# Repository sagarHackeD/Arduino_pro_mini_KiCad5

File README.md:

# Arduino_pro_mini_KiCad5
Arduino pro mini project in kicad 5

https://youtu.be/w0Ov9XtYdCo

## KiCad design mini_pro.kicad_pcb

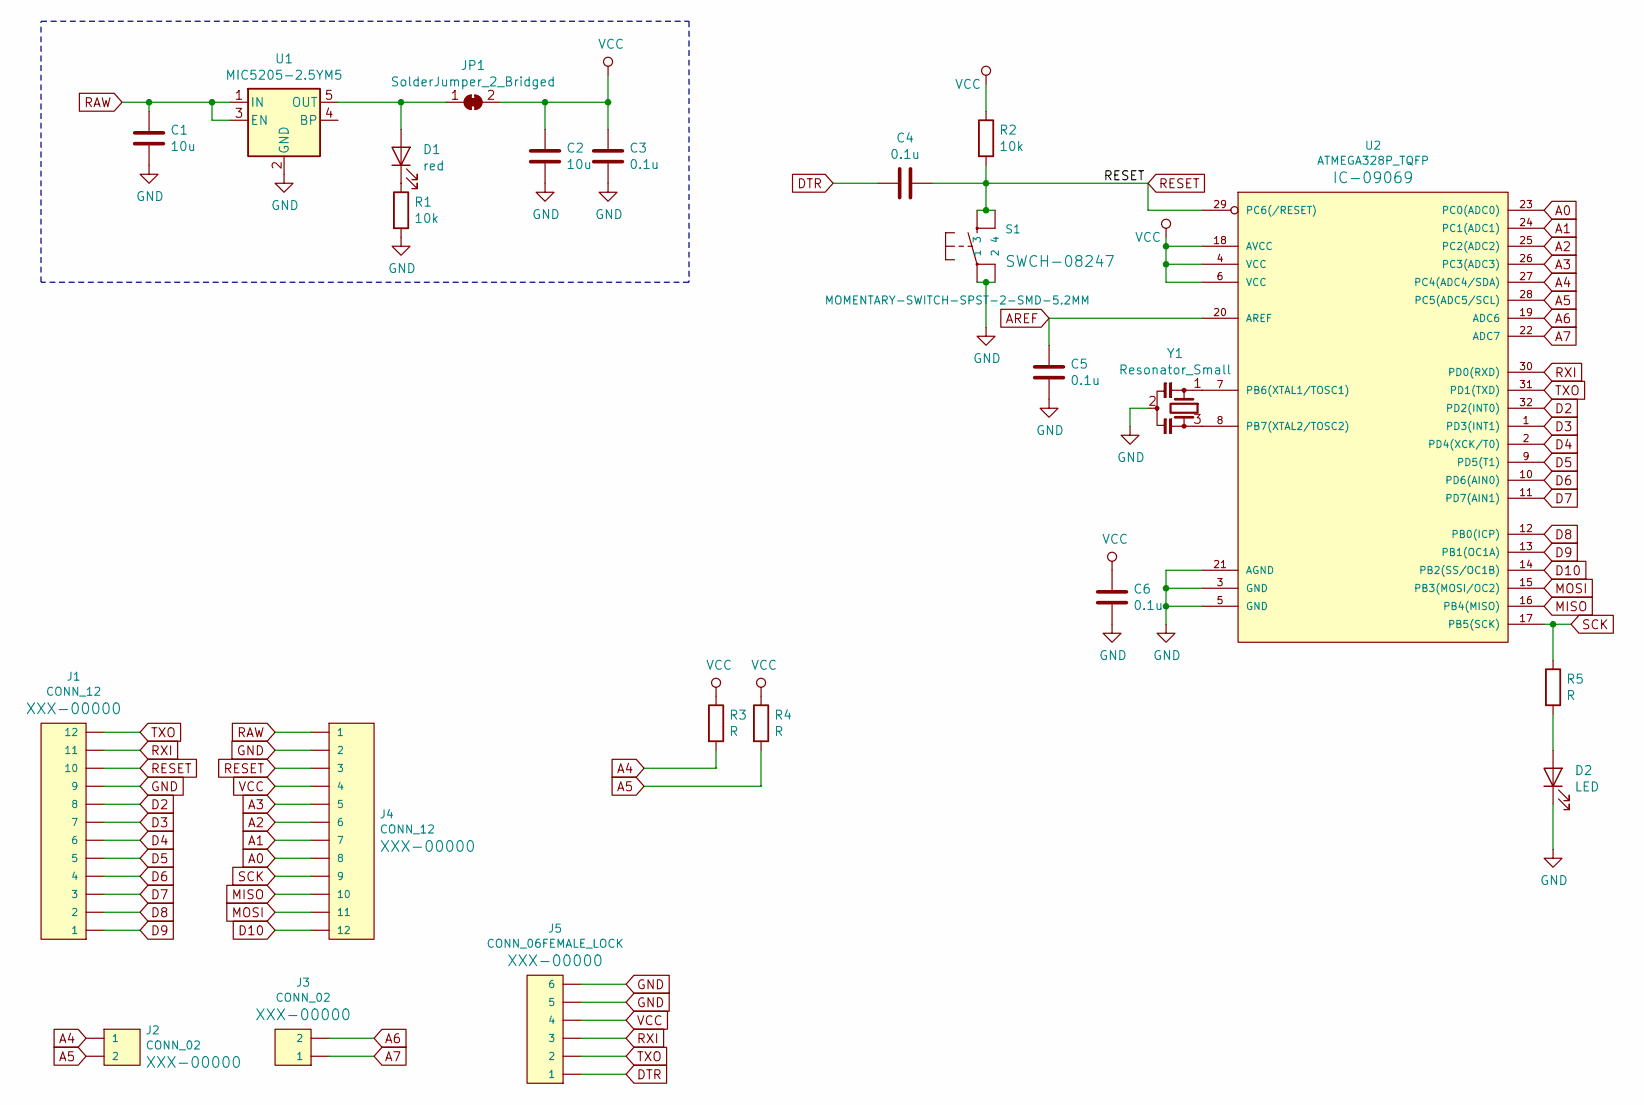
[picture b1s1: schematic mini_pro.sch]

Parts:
C1, C2: 10u; LED_1206_3216Metric
C3, C4, C5, C6: 0.1u; LED_0603_1608Metric
D1: red; LED_0603_1608Metric
D2: LED; LED_0603_1608Metric
J1, J4: CONN_12; 1X12
J2, J3: CONN_02; 1X02
J5: CONN_06FEMALE_LOCK; 1X06_FEMALE_LOCK.010
JP1: SolderJumper_2_Bridged; SolderJumper-2_P1.3mm_Bridged2Bar_Pad1.0x1.5mm
R1, R2: 10k; LED_0603_1608Metric
R3, R4, R5: R; LED_0603_1608Metric
S1: MOMENTARY-SWITCH-SPST-2-SMD-5.2MM; TACTILE_SWITCH_SMD_5.2MM
U1: MIC5205-2.5YM5; SOT-23-5
U2: ATMEGA328P_TQFP; TQFP32-08
Y1: Resonator_Small; RESONATOR-SMD-3.2X1.3

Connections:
A0: J4.8, U2.23 (PC0(ADC0))
A1: J4.7, U2.24 (PC1(ADC1))
A2: J4.6, U2.25 (PC2(ADC2))
A3: J4.5, U2.26 (PC3(ADC3))
A4: J2.1, R3.2, U2.27 (PC4(ADC4/SDA))
A5: J2.2, R4.2, U2.28 (PC5(ADC5/SCL))
A6: J3.2, U2.19 (ADC6)
A7: J3.1, U2.22 (ADC7)
AREF: C5.1, U2.20 (AREF)
D2: J1.8, U2.32 (PD2(INT0))
D3: J1.7, U2.1 (PD3(INT1))
D4: J1.6, U2.2 (PD4(XCK/T0))
D5: J1.5, U2.9 (PD5(T1))
D6: J1.4, U2.10 (PD6(AIN0))
D7: J1.3, U2.11 (PD7(AIN1))
D8: J1.2, U2.12 (PB0(ICP))
D9: J1.1, U2.13 (PB1(OC1A))
D10: J4.12, U2.14 (PB2(SS/OC1B))
DTR: C4.2, J5.1
GND: C1.2, C2.2, C3.2, C5.2, C6.2, D2.1 (K), J1.9, J4.2, J5.5, J5.6, R1.2, S1.1, S1.2, U1.2 (GND), U2.3 (GND), U2.5 (GND), U2.21 (AGND), Y1.2
MISO: J4.10, U2.16 (PB4(MISO))
MOSI: J4.11, U2.15 (PB3(MOSI/OC2))
unnamed: D1.1 (K), R1.1
unnamed: D1.2 (A), JP1.1 (A), U1.5 (OUT)
unnamed: D2.2 (A), R5.2
unnamed: U2.7 (PB6(XTAL1/TOSC1)), Y1.1
unnamed: U2.8 (PB7(XTAL2/TOSC2)), Y1.3
RAW: C1.1, J4.1, U1.1 (IN), U1.3 (EN)
RESET: C4.1, J1.10, J4.3, R2.2, S1.3, S1.4, U2.29 (PC6(/RESET))
RXI: J1.11, J5.3, U2.30 (PD0(RXD))
SCK: J4.9, R5.1, U2.17 (PB5(SCK))
TXO: J1.12, J5.2, U2.31 (PD1(TXD))
VCC: C2.1, C3.1, C6.1, J4.4, J5.4, JP1.2 (B), R2.1, R3.1, R4.1, U2.4 (VCC), U2.6 (VCC), U2.18 (AVCC)

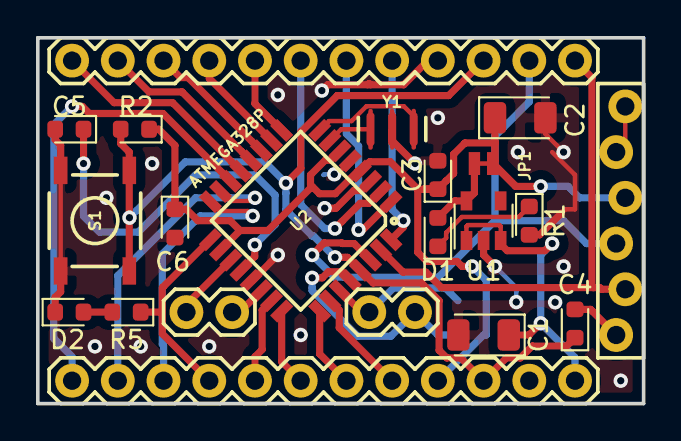
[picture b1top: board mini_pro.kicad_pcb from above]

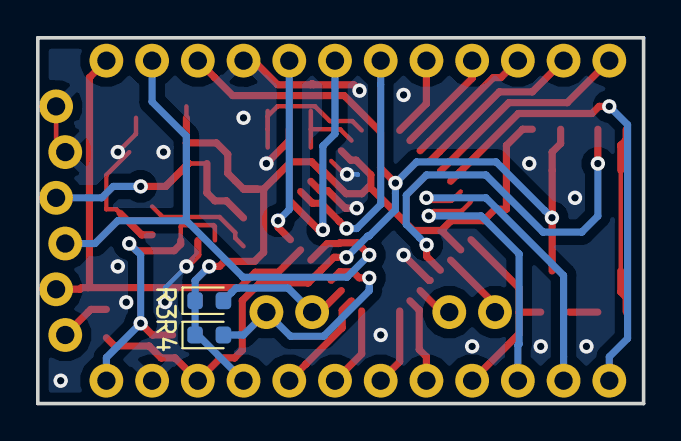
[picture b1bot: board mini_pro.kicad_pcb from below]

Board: 2 copper layers, 33.7 x 20.3 mm, 23 parts (2 on the bottom side), 33 nets.
